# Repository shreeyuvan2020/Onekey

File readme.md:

# The Onekey
 ## The one key and knob macropad(available at onekey.hackclub.com)
 ## Features
 - Sandwhich mount for constistency of feel
 - Magnetic Pogo Pin connectors for easily bonding the two sides of the macropad. 
 - Xiao RP2040 for cost efficiency
 - Neopixel for shiny
## Reasons I built this
 - @maxstellar on slack asked me to help with his internship project, so I did!
## Schematic
These schematics are very concise, it's just a MCU, whatever input device, and magnetic pogo pin connectors(generic symbol). Plus neopixel for key. First one is encoder, second is keyswitch
 - 
 - 
## PCB
 I designed the encoder PCB especially with a lot of care because the pcb had to stick out enough to reach into the case of the main onekey. The pcb with the key also took some time because at first I decided hotswap, but then changed to normal switches. I then made these basically centered. Also I had to work a bit on routing for the neopixel
  ### Keyswitch PCB
  
  ### Encoder PCB
  
## CAD
 I designed the CAD with portability, usability, and elegance in mind. I also had to design it with both a cutout for the USB and pogo pin connector. 
 ### Bottom Case of Encoder
 
 ### Top Plate of Encoder
 
 ### Bottom Case of Keyswitch
 
 ### Top Plate of Keyswitch
 
 ### Encoder Assembly
 
 ### Keyswitch Assembly
 
 ### Full Assembly
 
## Firmware
### The whole point of this YSWS is for people to create their own firmware for a one key macropad, so I don't have firmware here. 
## My Zine

Zine is at zine.pdf too, that might not load properly, try using chrome. Or download it and open. It's a known github issue.
## Assembly Instructions
 - First, obviously fabricate the PCB and solder everything.
 - Next is printing the plates and cases.
 - This is pretty simple, it was designed with tolerances, you can keep it at basically whatever setting
 - Put heatset inserts through the bottom of the cases
 - Then just screw the pcb and the bottom case together via those
 - Then put the plate on
 - Put the keycap on the switch
 - You have a Onekey!
## BOM
| Description                | Price             | Link                                                                                                                                                                                                                                                                                                                                                                                                                                                                                                                                                                                |
| :------------------------- | :---------------- | :---------------------------------------------------------------------------------------------------------------------------------------------------------------------------------------------------------------------------------------------------------------------------------------------------------------------------------------------------------------------------------------------------------------------------------------------------------------------------------------------------------------------------------------------------------------------------------- |
| Cherry MX Switch           | 0.89              | https://www.aliexpress.com/item/1005012226589276.html?                                                                                                                                                                                                                                                                                                                                                                                                                                                                                                                              |
| Rotary Encoder             | 0.77              | https://www.google.com/aclk?sa=L&ai=DChsSEwiDmf3MwqGVAxVMsgMAHSXIKaQYACICCAEQBhoCb2E&co=1&gclid=CjwKCAjwgO7RBhBKEiwAZNP85rsEmMWYl6g3VWZC5sRsF7ipgr_IHMzRDROKCq-PEOmagNYKbJWF8xoCA8UQAvD_BwE&cid=CAASugHkaLFY9NzucKKfRV9B6g7XEAqV9XkwZMdLsUDu2WDWrsWXZWfksITytF0U-4hzBTNQWbPV-MTb6yh8duZl9zGyLDUE2ipN-ISwgdL_gcXBXNhNxFtpJ2sveYj4UtoBmcYsorckyzbGdYKRD1rP_M9QV_JRDvF--RkA4PA8LLqQ30VgbJ3ZiJvVUGqgRd4tz5SxRPMyOoW_mR5yP6VgMLnE_8iheHBv7Mp09K1dmTv7WgK8nhcIEHBx4jw&cce=1&sig=AOD64_0N9GGjKSBzXkcAyZ8kAby49MiS1g&ctype=5&q=&ved=2ahUKEwiK2PXMwqGVAxUJkGoFHUd8NIgQ5bgDKAB6BAgJEBM&adurl= |
| Xiao RP2040                | 0.7               | https://www.aliexpress.us/item/3256804273304037.html?                                                                                                                                                                                                                                                                                                                                                                                                                                                                                                                               |
| Pair of Magnetic Pogo Conn | 6.5               |                                                                                                                                                                                                                                                                                                                                                                                                                                                                                                                                                                                     |
| PCBs from JLCPCB           | Will Cover Myself |                                                                                                                                                                                                                                                                                                                                                                                                                                                                                                                                                                                     |
| Total                      | 9.31              |                                                                                                                                                                                                                                                                                                                                                                                                                                                                                                                                                                                     |

## Credits
 This project was helped by @owais. Thanks to fallout for sponsoring this!

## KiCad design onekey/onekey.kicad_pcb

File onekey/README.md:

# The Chillboard
 ## The perfect ergonomic keyboard for chilling
 ## Features
 - Sandwhich mount for constistency of feel
 - Magnetic Pogo Pin connectors for easily bonding the two sides of the macropad. 
 - Xiao RP2040 for cost efficiency
 - Neopixel for shiny
## Reasons I built this
 - @maxstellar on slack asked me to help with his internship project, so I did!
## Schematic
These schematics are very concise, it's just a MCU, whatever input device, and magnetic pogo pin connectors(generic symbol). Plus neopixel for key. First one is encoder, second is keyswitch
 - 
 - 
## PCB
 I designed the encoder PCB especially with a lot of care because the pcb had to stick out enough to reach into the case of the main onekey. The pcb with the key also took some time because at first I decided hotswap, but then changed to normal switches. I then made these basically centered. Also I had to work a bit on routing for the neopixel
  ### Keyswitch PCB
  
  ### Encoder PCB
  
## CAD
 I designed the CAD with portability, usability, and elegance in mind. I also had to design it with both a cutout for the USB and pogo pin connector. 
 ### Bottom Case of Encoder
 
 ### Top Plate of Encoder
 
 ### Bottom Case of Keyswitch
 
 ### Top Plate of Keyswitch
 
 ### Encoder Assembly
 
 ### Keyswitch Assembly
 
 ### Full Assembly
 
## My Zine

Zine is at zine.pdf too
## Assembly Instructions
 - First, obviously fabricate the PCB and solder everything.
 - Next is printing the plates and cases.
 - This is pretty simple, it was designed with tolerances, you can keep it at basically whatever setting
 - Put heatset inserts through the bottom of the cases
 - Then just screw the pcb and the bottom case together via those
 - Then put the plate on
 - Put the keycap on the switch
 - You have a Onekey!

## Credits
 This project was helped by @owais. Thanks to fallout for sponsoring this!

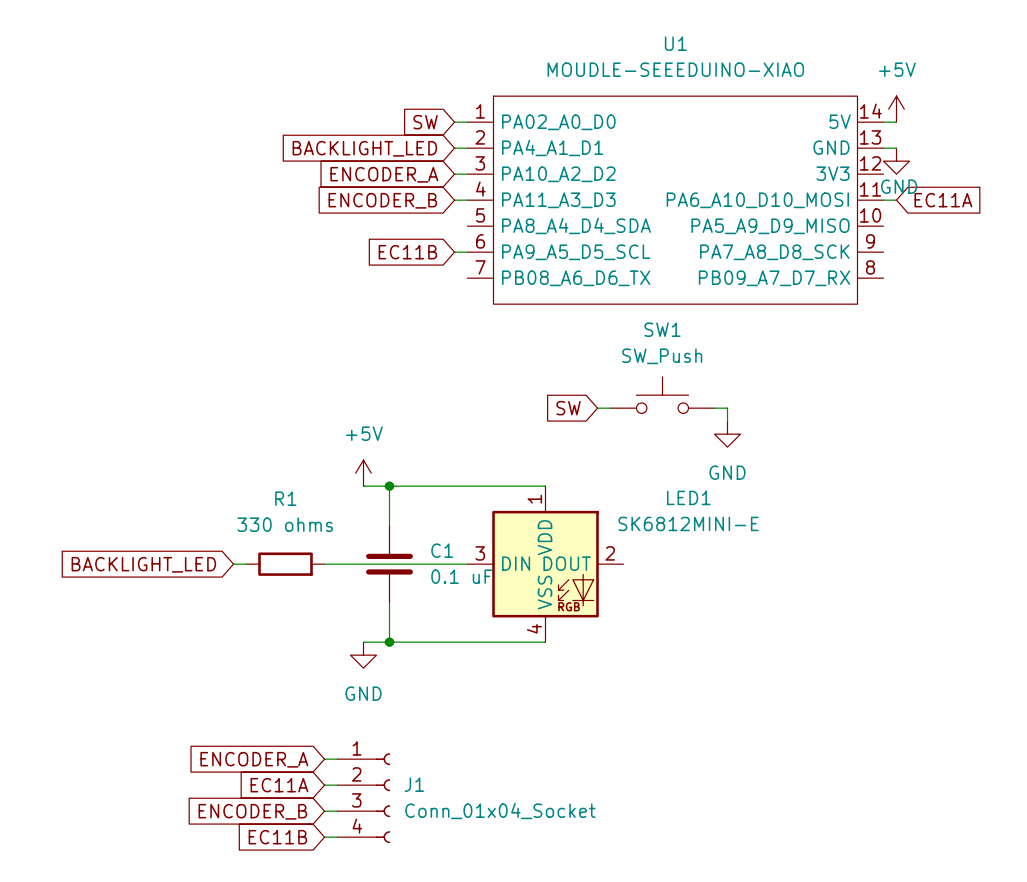
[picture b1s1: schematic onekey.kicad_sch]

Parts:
C1: 0.1 uF; C_0402_1005Metric
J1: Conn_01x04_Socket; MILL-MAX_829-22-003-20-001101
LED1: SK6812MINI-E; MX_SK6812MINI-E_REV
R1: 330 ohms; R_0402_1005Metric
SW1: SW_Push; SW_MX_1u
U1: MOUDLE-SEEEDUINO-XIAO; XIAO-Generic-Hybrid-14P-2.54-21X17.8MM

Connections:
+5V: C1.1, LED1.1 (VDD), U1.14 (5V)
BACKLIGHT_LED: R1.1, U1.2 (PA4_A1_D1)
EC11A: J1.2, U1.11 (PA6_A10_D10_MOSI)
EC11B: J1.4, U1.6 (PA9_A5_D5_SCL)
ENCODER_A: J1.1, U1.3 (PA10_A2_D2)
ENCODER_B: J1.3, U1.4 (PA11_A3_D3)
GND: C1.2, LED1.4 (VSS), SW1.2, U1.13 (GND)
unnamed: LED1.3 (DIN), R1.2
SW: SW1.1, U1.1 (PA02_A0_D0)

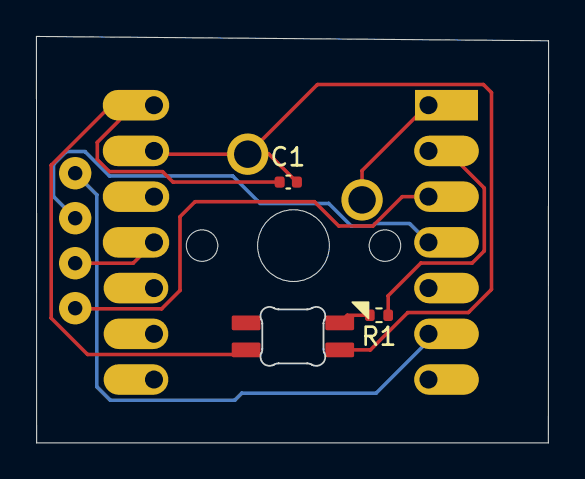
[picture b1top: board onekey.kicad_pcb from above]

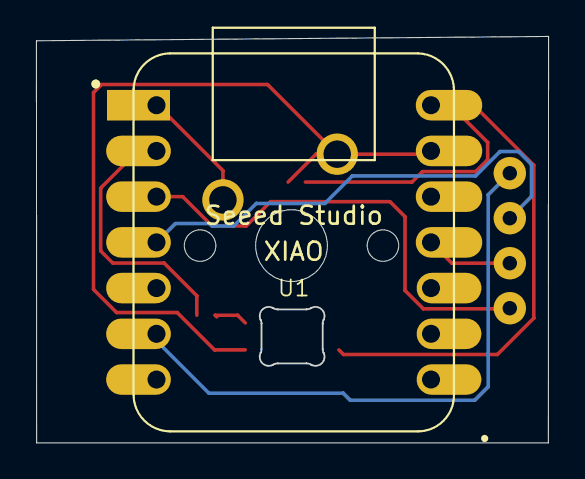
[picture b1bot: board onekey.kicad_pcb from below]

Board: 2 copper layers, 28.4 x 22.5 mm, 6 parts (4 on the bottom side), 9 nets.

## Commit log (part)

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2026-06-21 bleh
2026-06-21 start readme
2026-06-25 add link
2026-06-25 make it readable
2026-06-25 make it readable2
    Removed old entries and added new ones in the BOM.
2026-06-25 sdakljf
2026-06-25 add correct link
2026-06-25 Create test
2026-06-25 djahfj
2026-06-25 add readme
2026-06-25 hdkjsaf;k
2026-06-25 fix spaces
2026-06-25 fix zine
2026-06-25 make bom better
2026-06-25 make accurate
2026-06-25 add bom to readme
2026-06-25 djsafj
2026-06-25 Rename The one key and knob macropad-2.pdf to zine.pdf
2026-06-25 Rename The one key and knob macropad-2.png to zine.png
2026-06-25 update readme with firmware
2026-06-25 change zine stuff
